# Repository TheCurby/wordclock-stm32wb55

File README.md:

# Introduction
<div style="float:left;"></div>

**ℹ️`This wordclock project contains a simulator. This simulator is using the same sources as the STM32 project. So you can explore this project without building it.`**

**⚠️`This project contains some small smd parts. You should be able to solder VQFN parts.`**

This wordclock is based on a STM32WB55CEU6 microcontroller placed on a custom printed circuit board.
It is designed using the STM32CubeIDE without LL or HAL Driver, just CMSIS.
It is strongly encapsulated in classes and written in C++.
This project only provides a pcb and the firmware/software. An eclosure has to be designed by yourself.
You have to solder the LEDs directly on the pcb and no stripes are needed. You can use SK6812 or WS2812B.
You can use DS18B20 or DS18S20.

On the PCB are three capacitive touch sensors. The microcontroller provides the possibility to use internal touch sensors but I decided to use MTCH105 instead. The sensors are placed directly in copper. As an alternative there is a socket to plug in mechanical switches.

The STM32WB55CEU6 provides the possibility of BLE connectivity on chip. The antenna is implemented on the PCB. There is no app programmed yet and no support implemented in the firmware yet. Feel free to contribute this. 
The wordclock is designed to work without external tools like apps or remote control. The goal is that every functionality can be configured using the cap keys of the clock and an app should only be optional and should not deliver additional possibilities.

Of course you can use any DCF77 module you want. But the PCB and firmware is designed to use the following module: https://de.elv.com/dcf-empfangsmodul-dcf-2-091610

The clock can be powered using a 5V to 18V supply. 

<table border="0" style="border:0px;">
<tr><td>

</td><td>

</td></tr></table>

# ✔ Features
* Shows Time, Seconds and temperature (0.2°C steps using the dots to display)
* Enable / Disable the output like an old television with a red dot indicating
* Enable / Disable the DCF77 receiver
* Setting the clock manually
* Setting Color (RGBW)
  * Five different color modes:
    * Normal -> whole screen gets a color mixed by choosen colors
	* Each word gets a different color -> color is randomly mixed by choosen colors 
	* Each letter gets a different color -> color is randomly mixed by choosen colors 
	* Each word gets a different color -> one color from choosen colors 
	* Each letter gets a different color -> one color from choosen colors 
* Setting the LDR configuration for automatic luminosity correction
* Choosing the animation (switching between 5 minute steps)
  * No Animation
  * Random Animation
  * Fading in/out
  * Moving with random direction
  * Plopping randomly in/out
  * Falling down
  * Green Matrix
  * Teletype
* Enable / Disable night mode
* Supported languages: German, Dutch, English, Italian

# ⌛ In progress
* implementing languages (French, Spanish)
* finalize description
* implementing BLE support (firmware, app) and app connectivity
* commentating whole source code

# 🏁 Features planed for next version
None.
  
# ℹ️ Things that won't be implemented 
There are many wordclock projects out there. Many of them have hundreds of functionalities and are overengineered in my opinion. This project is meant to provide only useful features. So the following things **won't** be implemented:
Of course there is no guarantee that I will change my mind.

* Games like tetris etc.
* Updates over Air: Because everyone needs a ST-Link for Development/Deployment, it is very cheap and you can get it almost everywhere so buy it 😉
* Scrolling text and weather report: In my opinion the LED matrix is not suitable for this kind of stuff
* Overlays
* Sounds
* remote control: Because everyone has a smartphone today

# ⚠️ Issues
Firmware:
* Each dots gets different color if they should get the same in Colorful2 oder Word2 mode

# 💻 Simulator
The simulator of this project is using the same sources as the microcontroller project. Any changes in these sources will appear on the next build of the simulator. For this, the directory structure must remain the same.
The three bottons on the bottom correspond to the touch screens on the pcb of the wordclock.
The simulator is giving you some info what you can do with these buttons.

# 💾 Layouts
For every language there is a .svg file in the project. The font used is Source Code Pro Semibold. The .svg files have the right spaces between the letters and dots, but pay attention to the size and position of the frame and hidden elements. The .svg files are meant to use for plotters.

**Attention: Every front has a '°C' on the last line in __one__ letter place! In the tables below it takes __two__ places!**

<table>
	<tr>
		<td>English</td><td>German</td><td>Dutch</td><td>Italian</td><td>Spanish</td>
	</tr>
	<tr>
		<td><pre>IT-IS--AMPM
--QUARTER--
TWENTYFIVE-
HALF-TEN-TO
PAST---NINE
ONESIXTHREE
FOURFIVETWO
EIGHTELEVEN
SEVENTWELVE
TEN℃-OCLOCK</pre></td>
		<td><pre>ES-IST-AMPM
ZEHNZWANZIG
FÜNFVIERTEL
--NACHVOR--
HALB-ZWÖLF-
ZWEI-SIEBEN
-DREI--FÜNF
ELFNEUNVIER
-ACHTZEHN--
-SECHS℃-UHR</pre></td>
		<td><pre>HET-IS-VIJF
TIEN---AMPM
OVER--KWART
VOOR---OVER
HALF---ÉÉN-
TWEE---DRIE
VIERVIJFZES
ZEVEN-NEGEN
ACHTTIENELF
TWAALF℃-UUR</pre></td>
	<td><pre>SONO-LE----
È-LUNA-DUEZ
TREOTTONOVE
DIECIUNDICI
DODICISETTE
QUATTROCSEI
CINQUE-MENO
E-UN-QUARTO
VENTICINQUE
DIECI℃MEZZA
</pre></td>
	<td><pre>TODO</pre></td>
	</tr>
</table>

# 📃 Firmware
TODO: Description following like how to change the mapping of the leds or how to add animations ...

# PCB
The pcb is designed in KiCad. All libraries for symbols and footprints are delivered  with the project and there are no libs used directly from the KiCad installation.
Each LED has a 100nF capacitor but since there is a very big GND and +5V plane I never used or needed them. Nonetheless, it is **recommended** to equip them.

The board size is 370x370mm. The distances of the LEDs are:
* LED -> PCB edge: 50mm
* LED -> LED (x axis): 27mm
* LED -> LED (y axis): 30mm

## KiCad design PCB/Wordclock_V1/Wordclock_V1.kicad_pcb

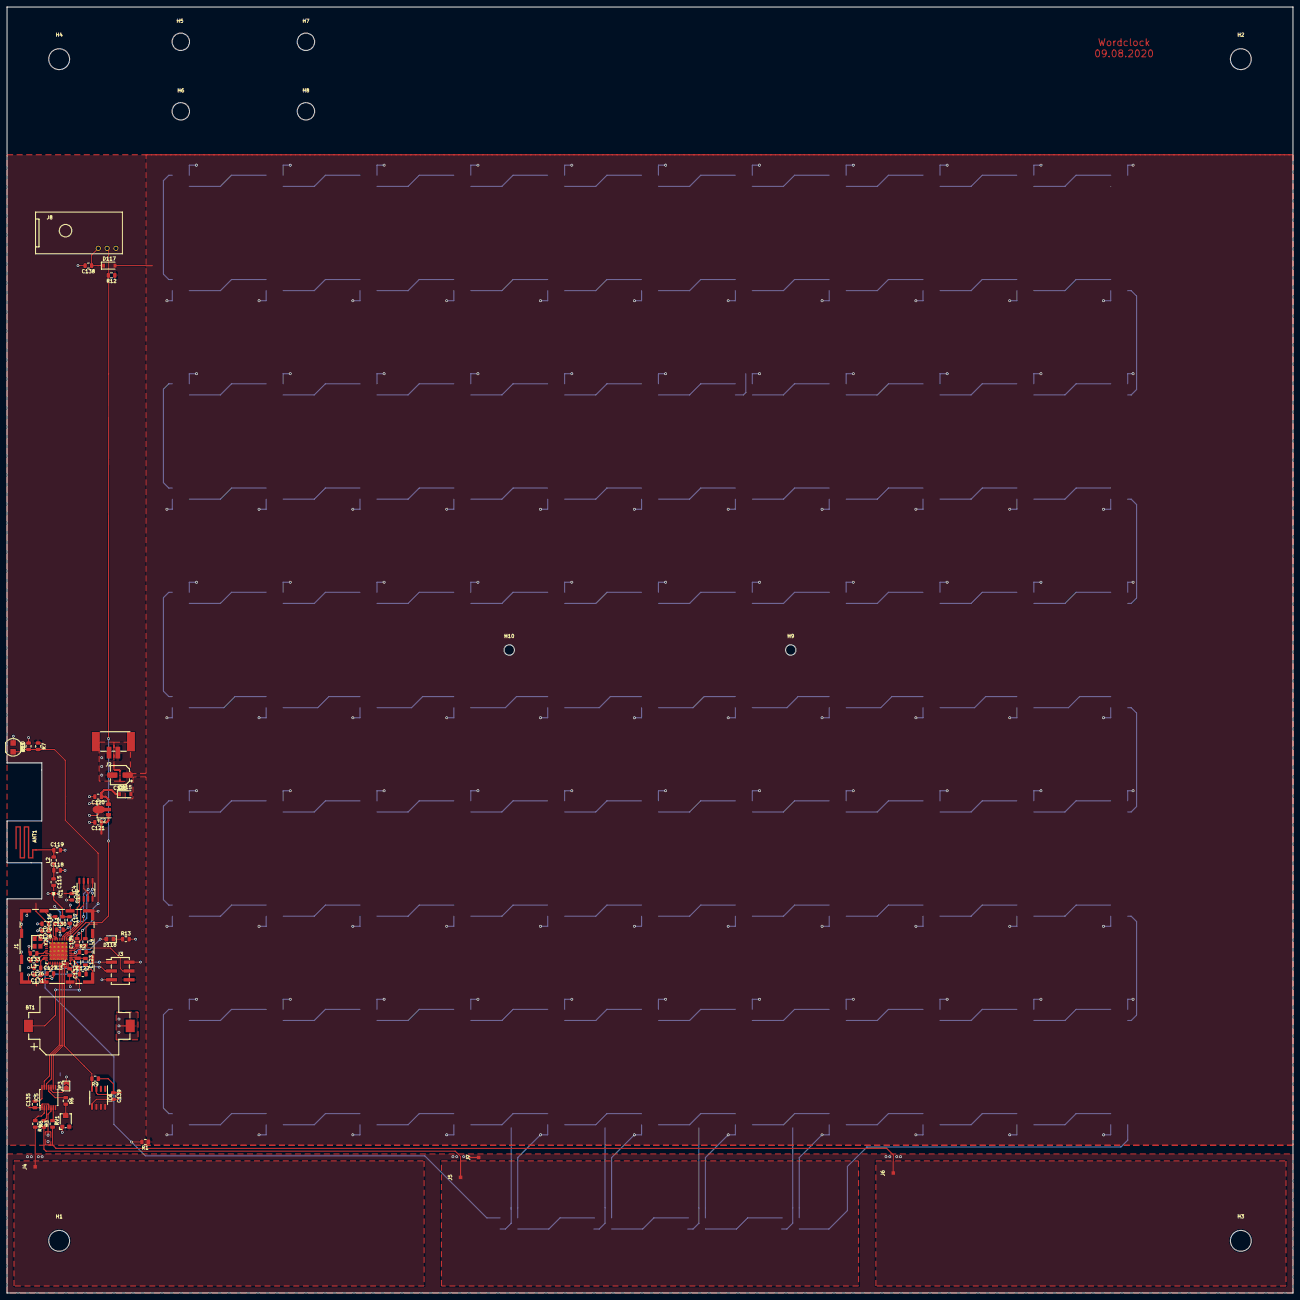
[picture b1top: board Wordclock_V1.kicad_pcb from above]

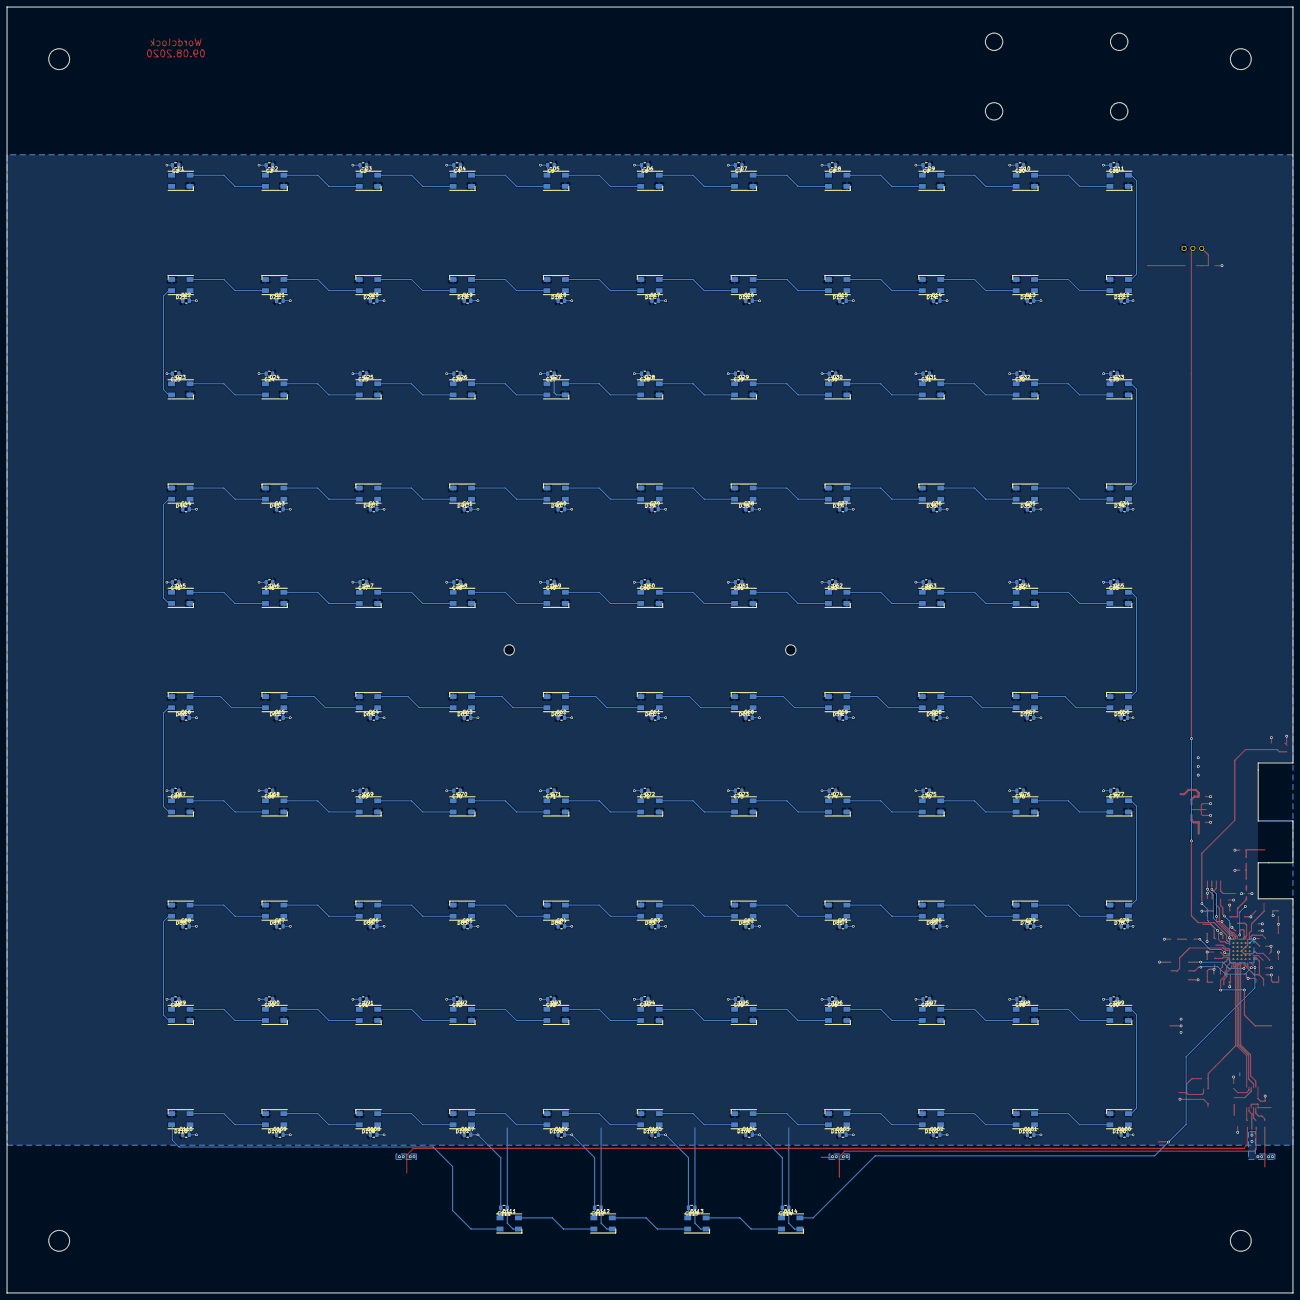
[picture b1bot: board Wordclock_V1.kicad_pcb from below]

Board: 2 copper layers, 370.0 x 370.0 mm, 300 parts (228 on the bottom side), 158 nets.

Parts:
ANT1: Antenna_BLE
BT1: 1060TR; BatteryHolder_Keystone_1060_1x2032
C1, C2, C3, C4, C5, C6, C7, C8, C9, C10, C11, C12, C13, C14, C15, C16, C17, C18, C19, C20, C21, C22, C23, C24, C25, C26, C27, C28, C29, C30, C31, C32, C33, C34, C35, C36, C37, C38, C39, C40, C41, C42, C43, C44, C45, C46, C47, C48, C49, C50, C51, C52, C53, C54, C55, C56, C57, C58, C59, C60, C61, C62, C63, C64, C65, C66, C67, C68, C69, C70, C71, C72, C73, C74, C75, C76, C77, C78, C79, C80, C81, C82, C83, C84, C85, C86, C87, C88, C89, C90, C91, C92, C93, C94, C95, C96, C97, C98, C99, C100, C101, C102, C103, C104, C105, C106, C107, C108, C109, C110, C111, C112, C113, C114: C; C_0805_2012Metric
C115: 10n; C_0805_2012Metric
C116, C118: 0.8p; C_0805_2012Metric
C117, C119: 0.3p; C_0805_2012Metric
C120, C121: 1u; C_0805_2012Metric
C122, C123: 6p; C_0805_2012Metric
C124, C127, C129, C130, C131, C132, C134, C135, C139: 100n; C_0805_2012Metric
C125: EEE-FK1C101SR (100u); CP_Elec_5x5.3
C126, C133, C138: 4u7; C_0805_2012Metric
C128: 100p; C_0805_2012Metric
D1, D2, D3, D4, D5, D6, D7, D8, D9, D10, D11, D12, D13, D14, D15, D16, D17, D18, D19, D20, D21, D22, D23, D24, D25, D26, D27, D28, D29, D30, D31, D32, D33, D34, D35, D36, D37, D38, D39, D40, D41, D42, D43, D44, D45, D46, D47, D48, D49, D50, D51, D52, D53, D54, D55, D56, D57, D58, D59, D60, D61, D62, D63, D64, D65, D66, D67, D68, D69, D70, D71, D72, D73, D74, D75, D76, D77, D78, D79, D80, D81, D82, D83, D84, D85, D86, D87, D88, D89, D90, D91, D92, D93, D94, D95, D96, D97, D98, D99, D100, D101, D102, D103, D104, D105, D106, D107, D108, D109, D110, D111, D112, D113, D114: SK6812; LED_SK6812_PLCC4_5.0x5.0mm_P3.2mm
D115, D117: BAS16GWX; D_SOD-123
D118: LED; LED_0805_2012Metric_Pad1.15x1.40mm_HandSolder
H1, H2, H3, H4: MountingHole; MountingHole_6mm
H5, H6, H7, H8: MountingHole_DCF77; MountingHole_5mm
H9, H10: MountingHole_DCF77; MountingHole_3mm
IC1: RFBPF1608070A0T
IC2: AP7365-33YG-13; SOT-89-3
IC3: STM32WB55CEU6; VQFN-48-1EP_7x7mm_P0.5mm_EP5.15x5.15mm_ThermalVias
IC4: M95M01-DFMN6TP; SO-8_3.9x4.9mm_P1.27mm
IC5: MTCH105-I/ST; TSSOP-14_4.4x5mm_P0.65mm
IC6: DS18B20Z+; SO-8_3.9x4.9mm_P1.27mm
J1: 36103205; Wuerth_36103205_20x20mm
J2: 1778764; TerminalBlock_Phoenix_PTSM-0,5-2-2,5-V-SMD_1x02-1MP_P2.50mm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
J3: TSM-103-01-T-DH-TR; PinHeader_2x03_P2.54mm_Vertical_SMD
J4: Taster1; pad
J5: Taster2; pad
J6: Taster3; pad
J7: Guard; pad
J8: DCF77; DCF77_ELV
JP3: Jumper; SolderJumper-2_P1.3mm_Open_TrianglePad1.0x1.5mm
L1, L2: ?; L_0805_2012Metric
L3: 10u; L_0805_2012Metric
L4: 47u; L_0805_2012Metric
R1: 470; R_0805_2012Metric
R2, R6, R10, R12: 10k; R_0805_2012Metric
R3, R4, R5, R7, R9: 4k7; R_0805_2012Metric
R11: Adafruit 161; R_LDR_4.9x4.2mm_P2.54mm_Vertical
R13: 1k; R_0805_2012Metric
RV1: TC33X-2-103E (20k); Potentiometer_Bourns_TC33X_Vertical
Y1: FC-135 32.7680KA-A; Crystal_Epson_FC135
Y2: ABM8AIG-32.000MHz-8-2Z-T; Crystal_SMD_Abracon_ABM8G-4Pin_3.2x2.5mm

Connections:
+3V3: C121.1, C124.1, C126.1, C127.1, C128.1, C129.1, C130.1, C131.1, C132.1, C135.1, C139.1, IC2.1, IC3.20, IC3.23, IC3.34, IC3.35, IC3.40, IC3.48, IC4.3, IC4.7, IC4.8, IC5.1, IC5.4, IC6.3, J3.6, L4.1, R7.1, R9.1, R12.1, RV1.3
+4V: C120.1, D115.1, IC2.3
+5V: C1.2, C2.2, C3.2, C4.2, C5.2, C6.2, C7.2, C8.2, C9.2, C10.2, C11.2, C12.2, C13.2, C14.2, C15.2, C16.2, C17.2, C18.2, C19.2, C20.2, C21.2, C22.2, C23.2, C24.2, C25.2, C26.2, C27.2, C28.2, C29.2, C30.2, C31.2, C32.2, C33.2, C34.2, C35.2, C36.2, C37.2, C38.2, C39.2, C40.2, C41.2, C42.2, C43.2, C44.2, C45.2, C46.2, C47.2, C48.2, C49.2, C50.2, C51.2, C52.2, C53.2, C54.2, C55.2, C56.2, C57.2, C58.2, C59.2, C60.2, C61.2, C62.2, C63.2, C64.2, C65.2, C66.2, C67.2, C68.2, C69.2, C70.2, C71.2, C72.2, C73.2, C74.2, C75.2, C76.2, C77.2, C78.2, C79.2, C80.2, C81.2, C82.2, C83.2, C84.2, C85.2, C86.2, C87.2, C88.2, C89.2, C90.2, C91.2, C92.2, C93.2, C94.2, C95.2, C96.2, C97.2, C98.2, C99.2, C100.2, C101.2, C102.2, C103.2, C104.2, C105.2, C106.2, C107.2, C108.2, C109.2, C110.2, C111.2, C112.2, C113.2, C114.2, C125.1, D1.3, D2.3, D3.3, D4.3, D5.3, D6.3, D7.3, D8.3, D9.3, D10.3, D11.3, D12.3, D13.3, D14.3, D15.3, D16.3, D17.3, D18.3, D19.3, D20.3, D21.3, D22.3, D23.3, D24.3, D25.3, D26.3, D27.3, D28.3, D29.3, D30.3, D31.3, D32.3, D33.3, D34.3, D35.3, D36.3, D37.3, D38.3, D39.3, D40.3, D41.3, D42.3, D43.3, D44.3, D45.3, D46.3, D47.3, D48.3, D49.3, D50.3, D51.3, D52.3, D53.3, D54.3, D55.3, D56.3, D57.3, D58.3, D59.3, D60.3, D61.3, D62.3, D63.3, D64.3, D65.3, D66.3, D67.3, D68.3, D69.3, D70.3, D71.3, D72.3, D73.3, D74.3, D75.3, D76.3, D77.3, D78.3, D79.3, D80.3, D81.3, D82.3, D83.3, D84.3, D85.3, D86.3, D87.3, D88.3, D89.3, D90.3, D91.3, D92.3, D93.3, D94.3, D95.3, D96.3, D97.3, D98.3, D99.3, D100.3, D101.3, D102.3, D103.3, D104.3, D105.3, D106.3, D107.3, D108.3, D109.3, D110.3, D111.3, D112.3, D113.3, D114.3, D115.2, D117.2, J2.2, R1.1
/CLK: IC3.14, IC4.6
/CS_E: IC3.13, IC4.1
/DQ: IC3.46, IC3.47, IC6.4, R9.2
/Guard: IC5.5, J7.1
/LDR: IC3.11, R7.2, R10.1, R11.2
/MISO: IC3.15, IC4.2
/MOSI: IC3.16, IC4.5
/MTO0: IC3.43, IC5.13
/MTO1: IC3.44, IC5.12
/MTO3: IC3.45, IC5.9
/NRST: IC3.7, J3.4
/SK6812: D114.2, IC3.37, R1.2
/SWCLK: IC3.41, J3.1
/SWDIO: IC3.39, J3.3
/T1: J4.1, R5.2
/T2: J5.1, R4.2
/T3: J6.1, R3.2
/TCO: IC3.12, J8.TCO, R12.2
GND: BT1.2, C1.1, C2.1, C3.1, C4.1, C5.1, C6.1, C7.1, C8.1, C9.1, C10.1, C11.1, C12.1, C13.1, C14.1, C15.1, C16.1, C17.1, C18.1, C19.1, C20.1, C21.1, C22.1, C23.1, C24.1, C25.1, C26.1, C27.1, C28.1, C29.1, C30.1, C31.1, C32.1, C33.1, C34.1, C35.1, C36.1, C37.1, C38.1, C39.1, C40.1, C41.1, C42.1, C43.1, C44.1, C45.1, C46.1, C47.1, C48.1, C49.1, C50.1, C51.1, C52.1, C53.1, C54.1, C55.1, C56.1, C57.1, C58.1, C59.1, C60.1, C61.1, C62.1, C63.1, C64.1, C65.1, C66.1, C67.1, C68.1, C69.1, C70.1, C71.1, C72.1, C73.1, C74.1, C75.1, C76.1, C77.1, C78.1, C79.1, C80.1, C81.1, C82.1, C83.1, C84.1, C85.1, C86.1, C87.1, C88.1, C89.1, C90.1, C91.1, C92.1, C93.1, C94.1, C95.1, C96.1, C97.1, C98.1, C99.1, C100.1, C101.1, C102.1, C103.1, C104.1, C105.1, C106.1, C107.1, C108.1, C109.1, C110.1, C111.1, C112.1, C113.1, C114.1, C116.2, C117.2, C118.2, C119.2, C120.2, C121.2, C122.2, C123.2, C124.2, C125.2, C126.2, C127.2, C128.2, C129.2, C130.2, C131.2, C132.2, C133.2, C134.2, C135.2, C138.2, C139.2, D1.1, D2.1, D3.1, D4.1, D5.1, D6.1, D7.1, D8.1, D9.1, D10.1, D11.1, D12.1, D13.1, D14.1, D15.1, D16.1, D17.1, D18.1, D19.1, D20.1, D21.1, D22.1, D23.1, D24.1, D25.1, D26.1, D27.1, D28.1, D29.1, D30.1, D31.1, D32.1, D33.1, D34.1, D35.1, D36.1, D37.1, D38.1, D39.1, D40.1, D41.1, D42.1, D43.1, D44.1, D45.1, D46.1, D47.1, D48.1, D49.1, D50.1, D51.1, D52.1, D53.1, D54.1, D55.1, D56.1, D57.1, D58.1, D59.1, D60.1, D61.1, D62.1, D63.1, D64.1, D65.1, D66.1, D67.1, D68.1, D69.1, D70.1, D71.1, D72.1, D73.1, D74.1, D75.1, D76.1, D77.1, D78.1, D79.1, D80.1, D81.1, D82.1, D83.1, D84.1, D85.1, D86.1, D87.1, D88.1, D89.1, D90.1, D91.1, D92.1, D93.1, D94.1, D95.1, D96.1, D97.1, D98.1, D99.1, D100.1, D101.1, D102.1, D103.1, D104.1, D105.1, D106.1, D107.1, D108.1, D109.1, D110.1, D111.1, D112.1, D113.1, D114.1, IC1.2, IC1.4, IC2.2, IC3.22, IC3.32, IC3.49, IC4.4, IC5.14, IC6.5, J1.1, J2.1, J3.2, J3.5, J8.GND, JP3.2, R2.2, R10.2, R11.1, R13.2, RV1.1, Y2.2, Y2.4
unnamed: ANT1.1, C119.1, L2.2
unnamed: BT1.1, IC3.1
unnamed: C115.1, C118.1, L2.1
unnamed: C115.2, IC1.3
unnamed: C116.1, IC3.21, L1.1
unnamed: C117.1, IC1.1, L1.2
unnamed: C122.1, IC3.2, Y1.1
unnamed: C123.1, IC3.3, Y1.2
unnamed: C133.1, IC3.31, L3.2
unnamed: C134.1, IC3.8, L4.2
unnamed: C138.1, D117.1, J8.VCC
unnamed: D1.2, D2.4
unnamed: D2.2, D3.4
unnamed: D3.2, D4.4
unnamed: D4.2, D5.4
unnamed: D5.2, D6.4
unnamed: D6.2, D7.4
unnamed: D7.2, D8.4
unnamed: D8.2, D9.4
unnamed: D10.2, D11.4
unnamed: D9.2, D10.4
unnamed: D11.2, D12.4
unnamed: D12.2, D13.4
unnamed: D13.2, D14.4
unnamed: D14.2, D15.4
unnamed: D15.2, D16.4
unnamed: D16.2, D17.4
unnamed: D17.2, D18.4
unnamed: D18.2, D19.4
unnamed: D19.2, D20.4
unnamed: D20.2, D21.4
unnamed: D21.2, D22.4
unnamed: D22.2, D23.4
unnamed: D23.2, D24.4
unnamed: D24.2, D25.4
unnamed: D25.2, D26.4
unnamed: D26.2, D27.4
unnamed: D27.2, D28.4
unnamed: D28.2, D29.4
unnamed: D29.2, D30.4
unnamed: D30.2, D31.4
unnamed: D31.2, D32.4
unnamed: D32.2, D33.4
unnamed: D33.2, D34.4
unnamed: D34.2, D35.4
unnamed: D35.2, D36.4
unnamed: D36.2, D37.4
unnamed: D37.2, D38.4
unnamed: D38.2, D39.4
unnamed: D39.2, D40.4
unnamed: D40.2, D41.4
unnamed: D41.2, D42.4
unnamed: D42.2, D43.4
unnamed: D43.2, D44.4
unnamed: D44.2, D45.4
unnamed: D45.2, D46.4
unnamed: D46.2, D47.4
unnamed: D47.2, D48.4
unnamed: D48.2, D49.4
unnamed: D49.2, D50.4
unnamed: D50.2, D51.4
unnamed: D51.2, D52.4
unnamed: D52.2, D53.4
unnamed: D53.2, D54.4
unnamed: D54.2, D55.4
unnamed: D55.2, D56.4
unnamed: D56.2, D57.4
unnamed: D57.2, D58.4
unnamed: D58.2, D59.4
unnamed: D59.2, D60.4
unnamed: D60.2, D61.4
unnamed: D61.2, D62.4
unnamed: D62.2, D63.4
unnamed: D63.2, D64.4
unnamed: D64.2, D65.4
unnamed: D65.2, D66.4
unnamed: D66.2, D67.4
unnamed: D67.2, D68.4
unnamed: D68.2, D69.4
unnamed: D69.2, D70.4
unnamed: D70.2, D71.4
unnamed: D71.2, D72.4
unnamed: D72.2, D73.4
unnamed: D73.2, D74.4
unnamed: D74.2, D75.4
unnamed: D75.2, D76.4
unnamed: D76.2, D77.4
unnamed: D77.2, D78.4
unnamed: D78.2, D79.4
unnamed: D79.2, D80.4
unnamed: D80.2, D81.4
unnamed: D81.2, D82.4
unnamed: D82.2, D83.4
unnamed: D83.2, D84.4
unnamed: D84.2, D85.4
unnamed: D85.2, D86.4
unnamed: D86.2, D87.4
unnamed: D87.2, D88.4
unnamed: D88.2, D89.4
unnamed: D89.2, D90.4
unnamed: D90.2, D91.4
unnamed: D91.2, D92.4
unnamed: D92.2, D93.4
unnamed: D93.2, D94.4
unnamed: D94.2, D95.4
unnamed: D95.2, D96.4
unnamed: D96.2, D97.4
unnamed: D97.2, D98.4
unnamed: D98.2, D99.4
unnamed: D100.2, D101.4
unnamed: D99.2, D100.4
unnamed: D101.2, D102.4
unnamed: D102.2, D103.4
unnamed: D103.2, D104.4
unnamed: D104.2, D105.4
unnamed: D105.2, D106.4
unnamed: D106.2, D107.4
unnamed: D107.2, D108.4
unnamed: D108.2, D109.4
unnamed: D109.2, D110.4
unnamed: D110.2, D111.4
unnamed: D111.2, D112.4
unnamed: D112.2, D113.4
unnamed: D113.2, D114.4
unnamed: D118.1, R13.1
unnamed: D118.2, IC3.5
unnamed: IC3.4, R2.1
unnamed: IC3.24, Y2.1
unnamed: IC3.25, Y2.3
unnamed: IC3.33, L3.1
unnamed: IC5.2, R5.1
unnamed: IC5.3, R4.1
unnamed: IC5.6, R3.1
unnamed: IC5.10, JP3.1
unnamed: IC5.11, R6.1
unnamed: R6.2, RV1.2

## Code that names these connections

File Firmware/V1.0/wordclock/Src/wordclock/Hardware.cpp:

#include "wordclock/Wordclock.hpp"

Hardware::Hardware() {
	/*##### RCC #####*/
	FLASH->ACR = 1;
	RCC->CR |= RCC_CR_HSEON;
	while (!(RCC->CR & RCC_CR_HSERDY));
	RCC->CFGR |= 0b10;
	while ((RCC->CFGR & (0b1000)) != 0b1000);
	RCC->CR &= ~(RCC_CR_HSION);

	PWR->CR1 |= PWR_CR1_DBP;
	PWR->CR1 |= 0b01ul << 9;
	if (!(RCC->BDCR & RCC_BDCR_LSERDY)) {
		RCC->BDCR |= RCC_BDCR_LSEON;
		while (!(RCC->BDCR & RCC_BDCR_LSERDY));
	}
	RCC->BDCR |= 0b01ul << 8;
	RCC->CCIPR |= 0x03ul << 28;
	PWR->CR4 |= PWR_CR4_C2BOOT;

	/* GPIOs */
	RCC->AHB2ENR |= RCC_AHB2ENR_GPIOAEN;
	RCC->AHB2ENR |= RCC_AHB2ENR_GPIOBEN;
	RCC->AHB2ENR |= RCC_AHB2ENR_GPIOEEN;

	STM32::configPinOutput(GPIOA, 0);    //..
	STM32::configPinOutput(GPIOA, 1);    //..
	STM32::configPinAnalog(GPIOA, 2);    //LDR
	STM32::configPinInput(GPIOA, 3);    //DCF77
	STM32::configPinOutput(GPIOA, 4);    //CS EEprom
	STM32::configPinAF(GPIOA, 5, (STM32::Flags) 5);    //SPI CLK
	STM32::configPinAF(GPIOA, 6, (STM32::Flags) 5);    //SPI MISO
	STM32::configPinAF(GPIOA, 7, (STM32::Flags) 5);    //SPI MOSI
	STM32::configPinOutput(GPIOA, 8);    //..
	STM32::configPinOutput(GPIOA, 9);    //..
	STM32::configPinOutput(GPIOA, 10);    //..
	STM32::configPin(GPIOA, 11, STM32::Flags::ALTERNATE, STM32::Flags::OPENDRAIN, STM32::Flags::NOPULL, (STM32::Flags) 1);    //SK6812 Timer
	STM32::configPinOutput(GPIOA, 12);    //..
	//STM32::configPin(GPIOA, 13, STM32::Flags::OUTPUT, STM32::Flags::PUSHPULL, STM32::Flags::NOPULL, 0);
	//STM32::configPin(GPIOA, 14, STM32::Flags::OUTPUT, STM32::Flags::PUSHPULL, STM32::Flags::NOPULL, 0);
	STM32::configPinOutput(GPIOA, 15);    //..
	STM32::configPinOutput(GPIOB, 0);    //..
	STM32::configPinOutput(GPIOB, 1);    //..
	STM32::configPinOutput(GPIOB, 2);    //..
	STM32::configPin(GPIOB, 3, STM32::Flags::INPUT, STM32::Flags::OPENDRAIN, STM32::Flags::PULLUP, (STM32::Flags) 0);    //MTO0
	STM32::configPin(GPIOB, 4, STM32::Flags::INPUT, STM32::Flags::OPENDRAIN, STM32::Flags::PULLUP, (STM32::Flags) 0);    //MTO1
	STM32::configPin(GPIOB, 5, STM32::Flags::INPUT, STM32::Flags::OPENDRAIN, STM32::Flags::PULLUP, (STM32::Flags) 0);    //MTO3
	STM32::configPin(GPIOB, 6, STM32::Flags::ALTERNATE, STM32::Flags::OPENDRAIN, STM32::Flags::NOPULL, (STM32::Flags) 7);    //OneWIre
	STM32::configPin(GPIOB, 7, STM32::Flags::ALTERNATE, STM32::Flags::OPENDRAIN, STM32::Flags::NOPULL, (STM32::Flags) 7);    //OneWIre
	STM32::configPinOutput(GPIOB, 8);    //..
	STM32::configPinOutput(GPIOB, 9);    //..
	STM32::configPinOutput(GPIOE, 4);    //..

	/* RTC */
	RCC->BDCR |= RCC_BDCR_RTCEN;

	/* SPI */
	RCC->APB2ENR |= RCC_APB2ENR_SPI1EN;

	/* Timer für Interrupt */
	RCC->APB1ENR1 |= RCC_APB1ENR1_TIM2EN;
	TIM2->ARR = 0xffffffff;
	TIM2->CNT = 0xffffffff;
	TIM2->DIER = TIM_DIER_UIE;
	TIM2->PSC = (CLK_TIMER / 1000000ul) - 1;
	TIM2->CR1 = TIM_CR1_CEN;
	STM32::setInterrupt(TIM2_IRQn, 1);

	/* Timer für SK6812 */
	RCC->APB2ENR |= RCC_APB2ENR_TIM1EN;
	RCC->AHB1ENR |= RCC_AHB1ENR_DMA1EN;
	RCC->AHB1ENR |= RCC_AHB1ENR_DMAMUX1EN;
	DMAMUX1_Channel0->CCR = 25;
	DMA1_Channel1->CCR =
	DMA_CCR_MINC | (0b00 << 10) | (0b01 << 8) | DMA_CCR_DIR;
	TIM1->CR1 = 0;
	TIM1->DIER = TIM_DIER_UDE;
	TIM1->CCMR2 = (0b110UL << 12) | TIM_CCMR2_OC4PE;
	TIM1->CCER = TIM_CCER_CC4E;
	TIM1->ARR = (CLK_TIMER / CLK_SK6812) - 1;
	TIM1->CCR4 = 0;
	TIM1->BDTR = TIM_BDTR_MOE;
	TIM1->CR1 = TIM_CR1_CEN;

	/* USART für OneWire */
	RCC->APB2ENR |= RCC_APB2ENR_USART1EN;

	/* LDR */
	RCC->AHB2ENR |= RCC_AHB2ENR_ADCEN;
	ADC1->CR &= ~ADC_CR_DEEPPWD;
	ADC1->CR |= ADC_CR_ADVREGEN;
	Timer t(10);
	while (!t.Ready());
	ADC1->CR |= ADC_CR_ADCAL;
	while (ADC1->CR & ADC_CR_ADCAL);
	ADC1->SMPR1 = (0b111ul << 21);
	ADC1->SQR1 = 7 << 6;
	ADC1->CR |= ADC_CR_ADEN;
	while (!(ADC1->ISR & ADC_ISR_ADRDY));
	ADC1->CFGR &= ~ADC_CFGR_JQDIS;
	ADC1->CR |= ADC_CR_ADSTART;

#ifndef DEBUG
	/* Watchdog */
	RCC->APB1ENR1 |= RCC_APB1ENR1_WWDGEN;
	WWDG->CFR = 0x7f;
	WWDG->CFR |= 0b111ul << 11;
	WWDG->CR = WWDG_CR_WDGA | 0x7f;
#endif
}

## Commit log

2020-10-18 init
2020-10-18 removed german comments
2020-10-18 moved tTemp Timer
2020-10-18 spelling readme
2020-10-18 Create LICENSE
2020-12-02 cleanup
2020-12-03 gerber
2020-12-12 refactoring, bugfixes
2020-12-23 stencil layouts
2020-12-26 en laser stencil
2020-12-26 docu
2020-12-26 it layout
2021-01-13 new animation
2021-01-14 timezone dcf77
2021-01-30 simulator
